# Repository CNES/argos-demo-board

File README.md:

# Argos Demo Board Using Arribada SMD Module

Demonstration and evaluation board designed to operate the **Arribada Argos SMD module** via USB and transmit **ARGOS uplink messages to the Kineis satellite constellation**.

---

> *© 2025/2026 CNES – Paul Miailhe.*  
> *This material is licensed under the CERN Open Hardware Licence Version 2 (CERN-OHL-S).*  
> *See licence: https://ohwr.org/licences/* 

> 
> 
> 
> 
> 
> 
---

---

## Introduction

This project presents an **Argos Transceiver Demonstration Board** intended for the evaluation, validation, and operation of the **Arribada Argos SMD module**.  
The board provides a compact and robust hardware platform to transmit **ARGOS uplink messages to the Kineis satellite constellation** using a standard **USB interface**.

Communication between the host computer and the Arribada SMD module is handled by a **FTDI FT231XQ USB-to-UART bridge**, directly interfacing with the module UART. This approach enables simple control of the transceiver using standard serial terminals or custom software tools.

The demonstration board integrates all essential functions required to operate the Arribada SMD module in a laboratory or development environment, including power supply conditioning, USB-to-UART communication, and RF interfacing. It is primarily intended to support early hardware validation, firmware development, and system-level testing of Argos communication chains prior to integration into a final embedded or avionics system.

This board targets engineers, students, and developers involved in **satellite communications, avionics, IoT, or space-related applications**, and may be used both as a standalone evaluation platform and as a reference hardware design.

---

> Inline with Arribada's open source philosophy, this board deliberately adopts a design distinct from the official demonstration hardware, focusing on simplicity and direct plug-and-play operation from a standard PC. The schematic and architecture are provided for reference, allowing potential users to reuse, adapt, or extend them according to their own needs..

---

## Hardware Design

### 1. Communication Architecture

Communication between the host PC and the **Arribada Argos SMD module** is performed through the module’s **UART interface**.  
This interface is used to send **AT commands** from a PC in order to configure the module and transmit **ARGOS uplink messages**. 
[→ See details on GitHub Arribada](https://github.com/arribada/argos-smd-at-kineis-firmware)

The USB-to-UART conversion is handled by a **FTDI FT231XQ USB 2.0 to UART bridge**. This device converts USB data received from a **virtual COM port** into UART signals fully compatible with the Arribada SMD module.

This architecture allows the board to be operated using:
- Standard serial terminal software
- Custom scripts
- Dedicated test or validation tools

No additional embedded controller is required, which simplifies early testing and debugging.

---

### 2. Power Supply Architecture

The card supports two power supply modes to suit different uses.

#### 2.1 Power Source Selection

Power source selection is performed using the **JP1 jumper**, which allows switching between:
- **VBUS → VDD (5V)** supplied by the **USB-C port**
- **VOUT → VDD (5V)** supplied via the **external power input on connector J1**

#### 2.2 External Power Protection

The external power input on **connector J1** is protected by:
- A **resettable PTC fuse 1206L050YR**
- A **LTC4365 protection circuit**

The **LTC4365** provides:
- **Reverse polarity protection**
- **Undervoltage protection** with a threshold set to **2.5 V**
- **Overvoltage protection** for input voltages exceeding **5 V**

#### 2.3 Power Regulation

After the protection stage, the power rail is distributed to two **TPS63900 buck-boost converters**:
- One converter supplies the **RF power amplifier (PA)** and is **enabled and controlled directly by the Arribada SMD module**
- The second converter is **always enabled** and provides the regulated **3.3 V supply** required for the **Arribada SMD module logic**

---

### 3. Connector Types

The Argos Demo Board uses the following connector families:

- **USB4085-GF-A (GCT)**  
  **USB Type-C receptacle (16-pin)** used for:
  - USB 2.0 communication with the host PC
  - Board power supply via **VBUS**

- **JST B2B-XH series**  
  **Through-hole wire-to-board connectors** used for:
  - External power input (**2.5 V to 5 V**)
  - Digital interfaces (**UART, SPI, GPIO – 3.3 V logic**)
  - General-purpose I/O connections

- **FTSH-105-01-L-DV-K (Samtec)**  
  **10-pin JTAG connector** used for:
  - Programming
  - Low-level debugging of the **Arribada Argos SMD module**
  - Access to **JTAG/SWD signals** of the embedded **STM32WL55**

- **60312002114503 (Würth Elektronik)**  
  **SMA 50 Ω RF connector** used for:
  - RF output connection
  - External antenna interface for the **ARGOS frequency band**
  - ⚠️ When transmitting, it is important to have at least a 50 Ohm load connected to the antenna output to protect against impedance mismatch. 

---

### 4. Functional Diagram

---
## Summary of the Bill of Materials (BOM) 

Components used on the board, with their official datasheets:

| Reference | Part Number | Role / Function | Datasheet |
|-----------|-------------|-----------------|-----------|
| D1, D7 | SMAJ15CA | TVS diode for surge and ESD protection | [→ Datasheet Littelfuse](https://www.littelfuse.com/assetdocs/tvs-diodes-smaj-datasheet?assetguid=13c2a823-03b8-4d1f-9ddc-9b44670aed9d) |
| F1, F2 | 1206L035/16YR | Resettable PTC fuse (overcurrent protection) | [→ Datasheet Littelfuse](https://www.littelfuse.com/assetdocs/resettable-ptcs-1206l-datasheet?assetguid=39a3f0c5-1a6b-4d52-9b9b-5c9c5f9c9c4a) |
| FB1, FB2 | BLM18KG601SN1D | Ferrite bead for EMI suppression | [→ Datasheet Murata](https://pim.murata.com/en-eu/pim/details/?partNum=BLM18KG601SN1%23) |
| L4 | 744232090 | Common-mode choke for USB line filtering | [→ Datasheet Würth Elektronik](https://www.we-online.com/components/products/datasheet/744232090.pdf) |
| Q1, Q2 | BSN20 | N-channel MOSFET for switching and protection | [→ Datasheet DIODES INC.](http://www.diodes.com/assets/Datasheets/ds31898.pdf) |
| SW1 | PTS647 | Momentary tactile push button switch | [→ Datasheet C&K](https://www.ckswitches.com/media/1471/pts647.pdf) |
| U2 | LTC4365DDB | Overvoltage, undervoltage and reverse polarity protection IC | [→ Datasheet Analog Devices](https://www.analog.com/media/en/technical-documentation/data-sheets/4365fa.pdf) |
| U3, U4 | TPS63900 | Buck-boost DC/DC converters | [→ Datasheet Texas Instruments](https://www.ti.com/lit/ds/symlink/tps63900.pdf) |
| U5 | 82400102 | Low-capacitance TVS diode array for USB protection | [→ Datasheet Würth Elektronik](https://www.we-online.com/components/products/datasheet/82400102.pdf) |
| U6 | FT231XQ | USB-to-UART bridge | [→ Datasheet FTDI](https://www.ftdichip.com/Support/Documents/DataSheets/ICs/DS_FT231X.pdf) |
| H4 | 3610213126S | RF shielding cabinet | [→ Datasheet Würth Elektronik](https://www.we-online.com/catalog/datasheet/3610213126S.pdf) |
| J8 | USB4085-GF-A | USB 2.0-only 16P Type-C Receptacle connector | [→ Datasheet GCT](https://www.usb.org/sites/default/files/documents/usb_type-c.zip) |
| J2 | 60312002114503 | Coaxial connector SMA | [→ Datasheet Würth Elektronik](https://www.we-online.com/components/products/datasheet/60312002114503.pdf?srsltid=AfmBOorv9MzbrmPnU-04R523FjHEC69xDMjVUBnj-GW9FHYse90msupc) |
| J4 | FTSH-105-01-L-DV-K | JTAG 10-PINS | [→ Datasheet Samtec](https://suddendocs.samtec.com/catalog_english/ftsh_smt.pdf?_gl=1*muazsd*_gcl_au*MTcxOTU2ODE1My4xNzY3ODg0MzAy*_ga*MTU3MjM5MTY3NS4xNzY3ODg0MzAz*_ga_3KFNZC07WW*czE3Njc4ODQzMDIkbzEkZzAkdDE3Njc4ODQzMDIkajYwJGwwJGgxMjE2ODMwMTY0) |
| J1, J3, J5, J6, J7 | B2B-XH | Through-hole wire-to-board connectors | [→ Datasheet JST](https://www.jst.fr/core/file.get?path=doc/jst/family/pdf/exh0125.pdf) |
| U1 | Argos SMD module | Transceiver Argos SMD for uplink Argos satellite | [→ Datasheet Arribada](https://github.com/arribada/featherwings-argos-smd-hw/wiki) |

---

## Getting Started

1. Connect the demonstration board to a host computer using a USB cable.
2. Install the **FTDI drivers** if required.
3. Select the desired **power input** using the **JP1 jumper**.
4. Connect an **antenna or a 50 Ω RF load** to the **SMA connector** before powering the board.
5. Open a **serial terminal** or a **custom software tool** on the host computer.
6. Configure the serial port according to the **Arribada Argos SMD module specifications**.
7. Send **AT commands** to configure the module and transmit **ARGOS uplink messages**.
8. If the board is operating correctly, the **5 V and 3.3 V LEDs** should be ON, and **TX/RX activity LEDs** should indicate serial communication.

Refer to the Arribada SMD module documentation for command syntax and operational details.

---

## Regulatory and Operational Notice

ARGOS transmissions are subject to regulatory constraints and operational authorization.

- Transmission over the ARGOS / Kineis constellation may require prior approval
- Users are responsible for ensuring compliance with applicable regulations
- This board does not grant any transmission rights by itself

---

## Mechanical Characteristics

- Dimensions: **80 × 50 mm**
- Maximum thickness: **13.5 mm**
- Mounting holes: 4 × Ø3.2 mm
- Weight without bracket: ** g**
- **STEP 3D** file available here:

---

## Regulatory and Operational Notice

ARGOS transmissions are subject to regulatory and operational constraints.

- Transmission over the ARGOS / Kineis constellation require prior authorization
- Users are responsible for regulatory compliance
- This board does **not** grant transmission rights by itself

---

## References & Resources

- **Arribada Initiative** – Official site  
  See link: <https://arribada.org>

- **Official Argos SMD Arduino Demo** – by Arribada  
  The full Arduino-based demonstration for the Argos SMD module is available on GitHub.  
  See link: <https://github.com/arribada/argos-smd-test-arduino>

- **Official Breakout Board FeatherWings** – by Arribada  
  This breakout board can be used with a Feather board (from Adafruit) to connect the ARGOS-SMD module.  
  It exposes the ARGOS-SMD module pins to the Feather board and includes a dedicated LDO to power the RF amplifier.  
  See link: <https://github.com/arribada/featherwings-argos-smd-hw>

- **Official Argos SMD Hardware Module** – by Arribada  
  The Arribada Argos SMD module is a compact **20 × 20 mm PCB** designed to operate as a standalone module or co-processor, enabling satellite communication via the **Kineis network**.  
  See link: <https://github.com/arribada/argos-smd-hw>

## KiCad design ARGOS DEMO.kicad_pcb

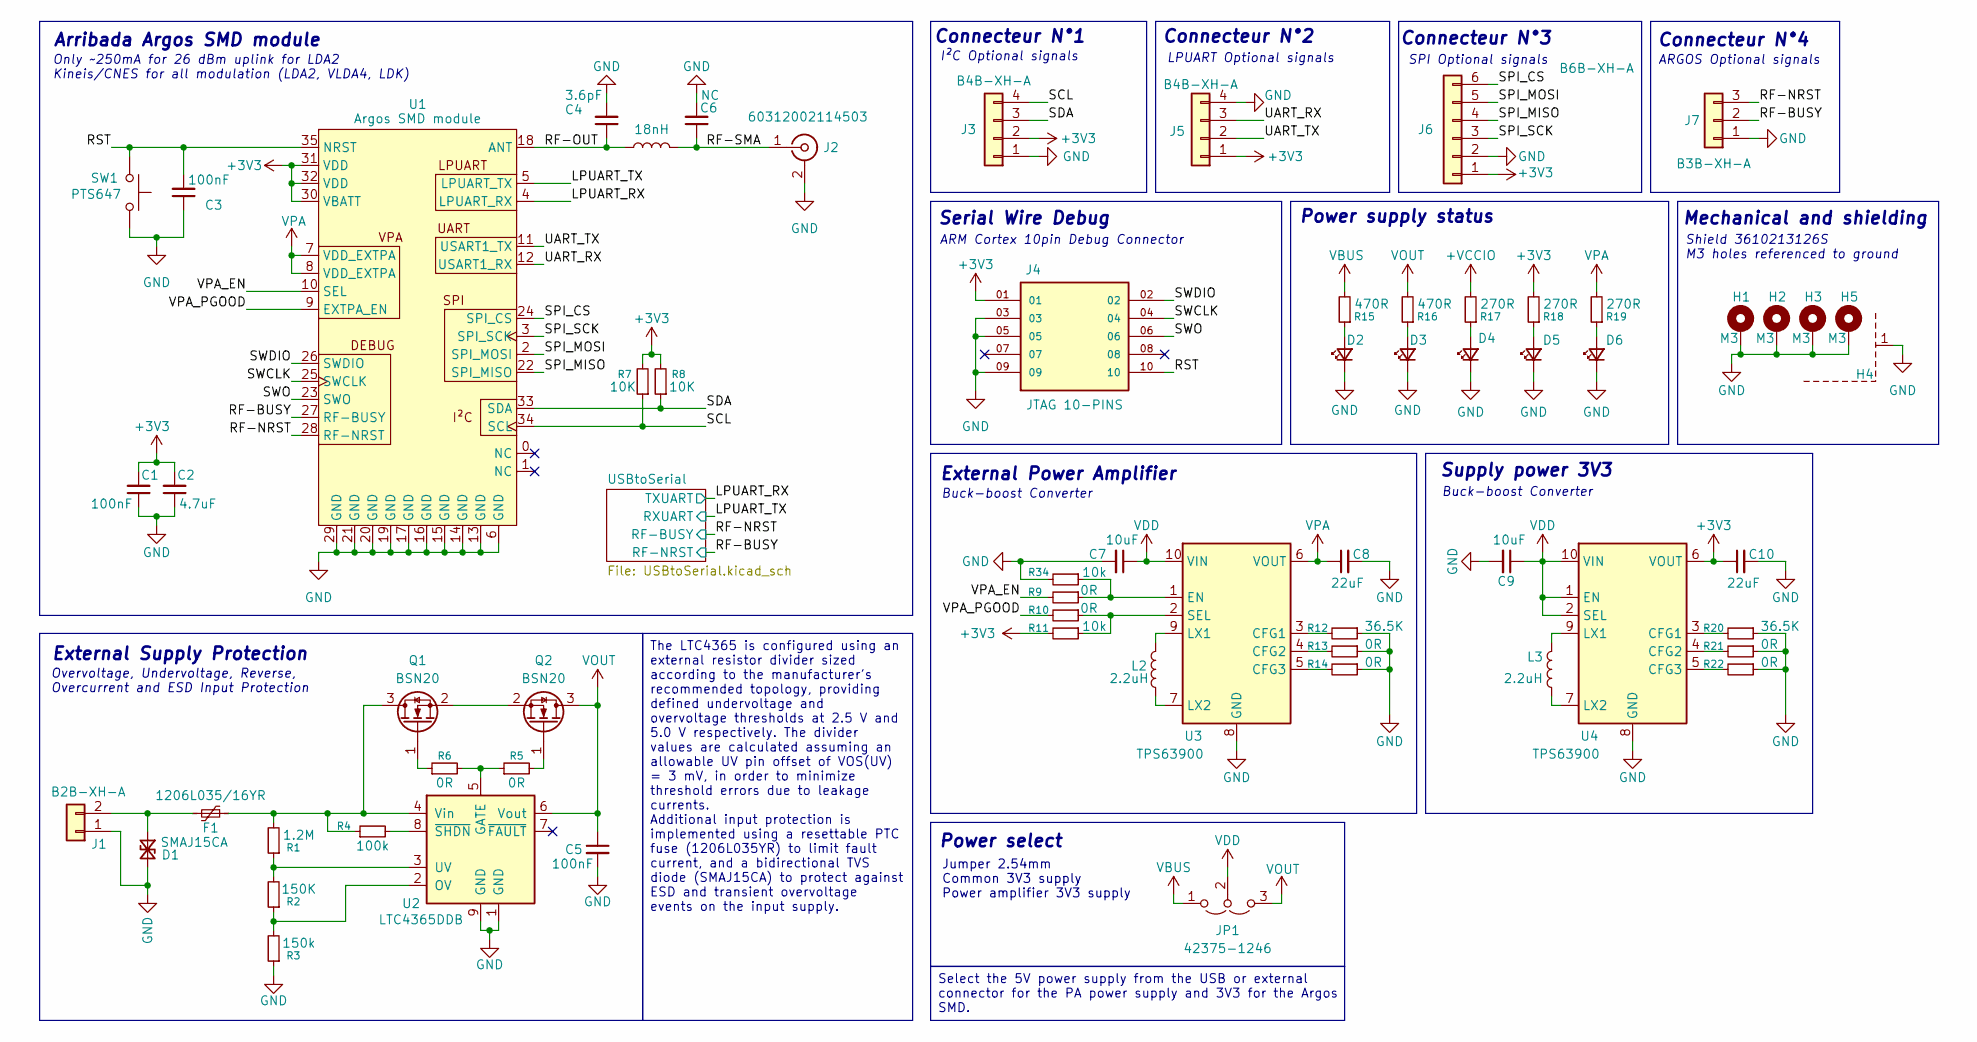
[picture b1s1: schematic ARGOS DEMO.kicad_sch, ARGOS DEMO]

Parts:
C1, C3, C5: 100nF; C_0603_1608Metric
C2: 4.7uF; C_0603_1608Metric
C4: 3.6pF; C_0603_1608Metric
C6: NC; C_0603_1608Metric
C7, C9: 10uF; C_0603_1608Metric
C8, C10: 22uF; C_0805_2012Metric
D1: SMAJ15CA; D_SMA
D2, D3, D4, D5, D6: LED_Small; LED_0603_1608Metric
F1: 1206L035/16YR; Fuse_1206_3216Metric
H1, H2, H3, H5: M3; MountingHole_3.2mm_M3_DIN965_Pad
H4: 3610213126S; H_Wurth_WE-SHC-SMT-FRAME_36103255S; Part Number 3610213126S
J1: B2B-XH-A; JST_XH_B2B-XH-A_1x02_P2.50mm_Vertical
J2: 60312002114503; SMA_Wurth_60312002114503_Vertical
J3, J5: B4B-XH-A; JST_XH_B4B-XH-A_1x04_P2.50mm_Vertical
J4: JTAG 10-PINS; SAMTEC_FTSH-105-XX-X-DV
J6: B6B-XH-A; JST_XH_B6B-XH-A_1x06_P2.50mm_Vertical
J7: B3B-XH-A; JST_XH_B3B-XH-A_1x03_P2.50mm_Vertical
JP1: 42375-1246; PinHeader_1x03_P2.54mm_Vertical
L1: 18nH; L_0603_1608Metric
L2, L3: 2.2uH; L_1008_2520Metric
Q1, Q2: BSN20; SOT-23
R1: 1.2M; R_0603_1608Metric
R2: 150K; R_0603_1608Metric
R3: 150k; R_0603_1608Metric
R4: 100k; R_0603_1608Metric
R5, R6, R9, R10, R13, R14, R21, R22: 0R; R_0603_1608Metric
R7, R8: 10K; R_0603_1608Metric
R11, R34: 10k; R_0603_1608Metric
R12, R20: 36.5K; R_0603_1608Metric
R15, R16: 470R; R_0603_1608Metric
R17, R18, R19: 270R; R_0603_1608Metric
SW1: PTS647; SW_SPST_PTS647_Sx38
U1: Argos SMD module; SMD ARGOS
U2: LTC4365DDB; DFN-8-1EP_2x3mm_P0.5mm_EP0.61x2.2mm
U3, U4: TPS63900; WSON-10-1EP_2.5x2.5mm_P0.5mm_EP1.2x2mm

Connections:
+3V3: C1.2, C2.2, C10.1, J3.2, J4.01, J5.1, J6.1, R7.2, R8.2, R11.2, R18.2, U1.30 (VBATT), U1.31 (VDD), U1.32 (VDD), U4.6 (VOUT)
+VCCIO: R17.2; also elsewhere on the board
/LPUART_RX: U1.4 (LPUART_RX); also elsewhere on the board
/LPUART_TX: U1.5 (LPUART_TX); also elsewhere on the board
/RF-BUSY: J7.2, U1.27 (RF-BUSY); also elsewhere on the board
/RF-NRST: J7.3, U1.28 (RF-NRST); also elsewhere on the board
/RF-OUT: C4.1, L1.1, U1.18 (ANT)
/RF-SMA: C6.1, J2.1 (In), L1.2
/RST: C3.2, J4.10, SW1.1, U1.35 (NRST)
/SCL: J3.4, R7.1, U1.34 (SCL)
/SDA: J3.3, R8.1, U1.33 (SDA)
/SPI_CS: J6.6, U1.24 (SPI_CS)
/SPI_MISO: J6.4, U1.22 (SPI_MISO)
/SPI_MOSI: J6.5, U1.2 (SPI_MOSI)
/SPI_SCK: J6.3, U1.3 (SPI_SCK)
/SWCLK: J4.04, U1.25 (SWCLK)
/SWDIO: J4.02, U1.26 (SWDIO)
/SWO: J4.06, U1.23 (SWO)
/UART_RX: J5.3, U1.12 (USART1_RX)
/UART_TX: J5.2, U1.11 (USART1_TX)
/VPA_EN: R9.2, U1.10 (SEL)
/VPA_PGOOD: R10.2, U1.9 (EXTPA_EN)
GND: C1.1, C2.1, C3.1, C4.2, C5.2, C6.2, C7.2, C8.2, C9.2, C10.2, D1.2 (A2), D2.1 (K), D3.1 (K), D4.1 (K), D5.1 (K), D6.1 (K), H1.1, H2.1, H3.1, H4.1 (GND), H5.1, J1.1, J2.2 (Ext), J3.1, J4.03, J4.05, J4.09, J5.4, J6.2, J7.1, R3.1, R12.1, R13.1, R14.1, R20.1, R21.1, R22.1, R34.2, SW1.2, U1.6 (GND), U1.13 (GND), U1.14 (GND), U1.15 (GND), U1.16 (GND), U1.17 (GND), U1.19 (GND), U1.20 (GND), U1.21 (GND), U1.29 (GND), U2.1 (GND), U2.9 (GND), U3.8 (GND), U3.11 (GND), U4.8 (GND), U4.11 (GND); also elsewhere on the board
unnamed: D1.1 (A1), F1.2, J1.2
unnamed: D2.2 (A), R15.1
unnamed: D3.2 (A), R16.1
unnamed: D4.2 (A), R17.1
unnamed: D5.2 (A), R18.1
unnamed: D6.2 (A), R19.1
unnamed: F1.1, Q1.3 (D), R1.2, R4.1, U2.4 (Vin)
unnamed: Q1.1 (G), R6.1
unnamed: Q1.2 (S), Q2.2 (S)
unnamed: Q2.1 (G), R5.2
unnamed: R5.1, R6.2, U2.5 (GATE)
unnamed: R2.1, R3.2, U2.2 (OV)
unnamed: R1.1, R2.2, U2.3 (UV)
unnamed: R4.2, U2.8 (~SHDN)
unnamed: R12.2, U3.3 (CFG1)
unnamed: R13.2, U3.4 (CFG2)
unnamed: R14.2, U3.5 (CFG3)
unnamed: R9.1, R34.1, U3.1 (EN)
unnamed: L2.2, U3.9 (LX1)
unnamed: L2.1, U3.7 (LX2)
unnamed: R10.1, R11.1, U3.2 (SEL)
unnamed: R20.2, U4.3 (CFG1)
unnamed: R21.2, U4.4 (CFG2)
unnamed: R22.2, U4.5 (CFG3)
unnamed: L3.2, U4.9 (LX1)
unnamed: L3.1, U4.7 (LX2)
VBUS: JP1.1 (A), R15.2; also elsewhere on the board
VDD: C7.1, C9.1, JP1.2 (C), U3.10 (VIN), U4.1 (EN), U4.2 (SEL), U4.10 (VIN)
VOUT: C5.1, JP1.3 (B), Q2.3 (D), R16.2, U2.6 (Vout)
VPA: C8.1, R19.2, U1.7 (VDD_EXTPA), U1.8 (VDD_EXTPA), U3.6 (VOUT)

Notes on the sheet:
SPI Optional signals
Shield 3610213126S M3 holes referenced to ground
ARGOS Optional signals
Connecteur N°3
Mechanical and shielding
External Power Amplifier
Serial Wire Debug
Overvoltage, Undervoltage, Reverse, Overcurrent and ESD Input Protection
Connecteur N°1
Connecteur N°2
I²C Optional signals
Supply power 3V3
Buck-boost Converter
Jumper 2.54mm Common 3V3 supply Power amplifier 3V3 supply
Power select
Only ~250mA for 26 dBm uplink for LDA2 Kineis/CNES for all modulation (LDA2, VLDA4, LDK)
Power supply status
Connecteur N°4
Arribada Argos SMD module
LPUART Optional signals
External Supply Protection
ARM Cortex 10pin Debug Connector
Select the 5V power supply from the USB or external connector for the PA power supply and 3V3 for the Argos SMD.
The LTC4365 is configured using an external resistor divider sized according to the manufacturer's recommended topology, providing defined undervoltage and overvoltage thresholds at 2.5 V and 5.0 V respectively. The divider values are calculated assuming an allowable UV pin offset of VOS(UV) = 3 mV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

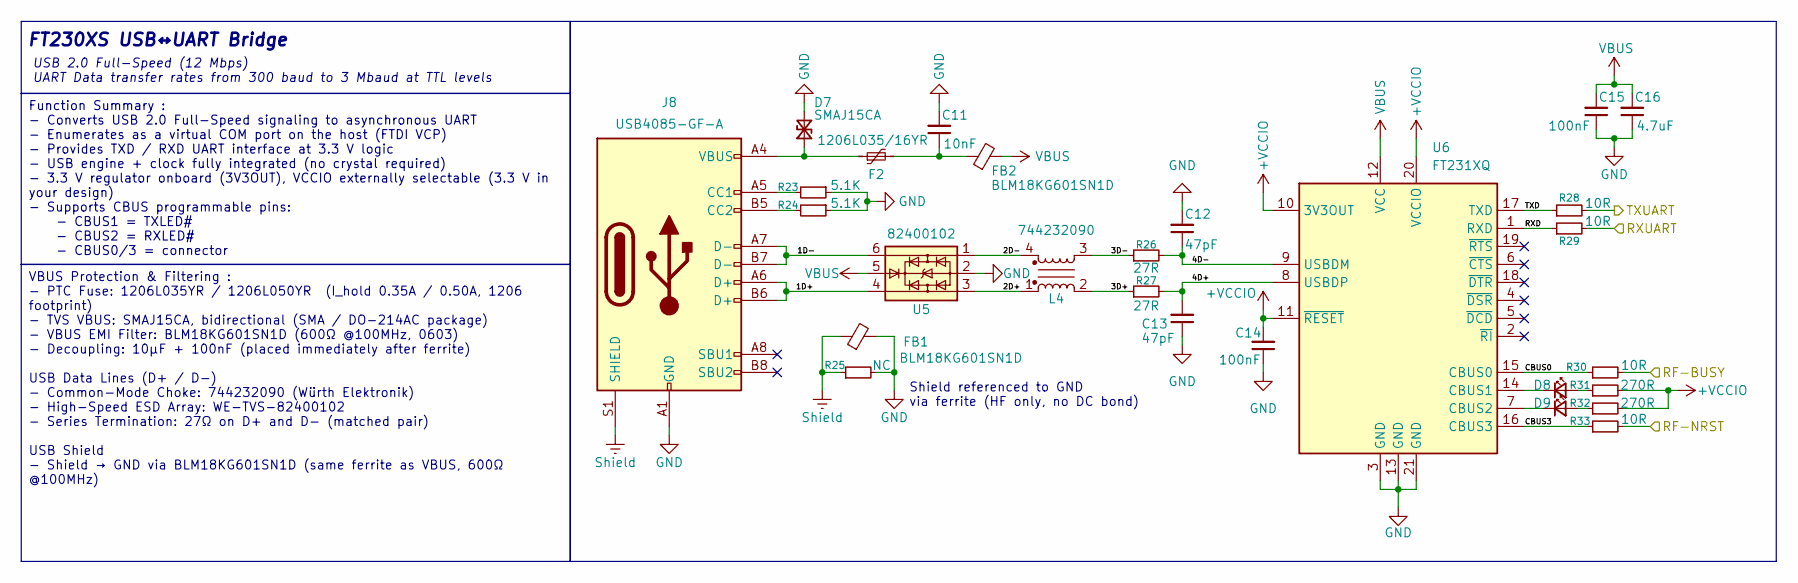
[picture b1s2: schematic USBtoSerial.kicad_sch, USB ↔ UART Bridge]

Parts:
C11: 10nF; C_0603_1608Metric
C12, C13: 47pF; C_0603_1608Metric
C14, C15: 100nF; C_0603_1608Metric
C16: 4.7uF; C_0603_1608Metric
D7: SMAJ15CA; D_SMA
D8, D9: LED_Small; LED_0603_1608Metric
F2: 1206L035/16YR; Fuse_1206_3216Metric
FB1, FB2: BLM18KG601SN1D; L_0603_1608Metric
J8: USB4085-GF-A; CONN16_USB4085-GF-A_GCT
L4: 744232090; L_CommonMode_Wurth_WE-CNSW-1206
R23, R24: 5.1K; R_0603_1608Metric
R25: NC; R_0603_1608Metric
R26, R27: 27R; R_0603_1608Metric
R28, R29, R30, R33: 10R; R_0603_1608Metric
R31, R32: 270R; R_0603_1608Metric
U5: 82400102; SOT-23-6
U6: FT231XQ; QFN-20-1EP_4x4mm_P0.5mm_EP2.5x2.5mm

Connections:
+VCCIO: C14.2, R31.2, R32.2, U6.10 (3V3OUT), U6.11 (~RESET), U6.20 (VCCIO); also elsewhere on the board
/LPUART_RX: R28.2; also elsewhere on the board
/LPUART_TX: R29.2; also elsewhere on the board
/RF-BUSY: R33.2; also elsewhere on the board
/RF-NRST: R30.2; also elsewhere on the board
/USBtoSerial/1D+: J8.A6 (D+), J8.B6 (D+), U5.4
/USBtoSerial/1D-: J8.A7 (D-), J8.B7 (D-), U5.6
/USBtoSerial/2D+: L4.1, U5.3
/USBtoSerial/2D-: L4.4, U5.1
/USBtoSerial/3D+: L4.2, R27.1
/USBtoSerial/3D-: L4.3, R26.1
/USBtoSerial/4D+: C13.2, R27.2, U6.8 (USBDP)
/USBtoSerial/4D-: C12.1, R26.2, U6.9 (USBDM)
/USBtoSerial/CBUS0: R30.1, U6.15 (CBUS0)
/USBtoSerial/CBUS3: R33.1, U6.16 (CBUS3)
/USBtoSerial/RXD: R29.1, U6.1 (RXD)
/USBtoSerial/TXD: R28.1, U6.17 (TXD)
GND: C11.2, C12.2, C13.1, C14.1, C15.1, C16.1, D7.2 (A2), FB1.2, J8.A1 (GND), J8.A12 (GND), J8.B1 (GND), J8.B12 (GND), R23.1, R24.1, R25.2, U5.2, U6.3 (GND), U6.13 (GND), U6.21 (GND); also elsewhere on the board
unnamed: C11.1, F2.2, FB2.1
unnamed: D7.1 (A1), F2.1, J8.A4 (VBUS), J8.A9 (VBUS), J8.B4 (VBUS), J8.B9 (VBUS)
unnamed: D8.2 (A), R31.1
unnamed: D8.1 (K), U6.14 (CBUS1)
unnamed: D9.2 (A), R32.1
unnamed: D9.1 (K), U6.7 (CBUS2)
unnamed: J8.A5 (CC1), R23.2
unnamed: J8.B5 (CC2), R24.2
Shield: FB1.1, J8.S1 (SHIELD), R25.1
VBUS: C15.2, C16.2, FB2.2, U5.5, U6.12 (VCC); also elsewhere on the board

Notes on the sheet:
USB 2.0 Full-Speed (12 Mbps) UART Data transfer rates from 300 baud to 3 Mbaud at TTL levels
Shield referenced to GND via ferrite (HF only, no DC bond)
FT230XS USB↔UART Bridge
Function Summary : - Converts USB 2.0 Full-Speed signaling to asynchronous UART - Enumerates as a virtual COM port on the host (FTDI VCP) - Provides TXD / RXD UART interface at 3.3 V logic - USB engine + clock fully integrated (no crystal required) - 3.3 V regulator onboard (3V3OUT), VCCIO external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
VBUS Protection & Filtering : - PTC Fuse: 1206L035YR / 1206L050YR (I_hold 0.35A / 0.50A, 1206 footprint) - TVS VBUS: SMAJ15CA, bidirectional (SMA / DO-214AC package) - VBUS EMI Filter: BLM18KG601SN1D (600Ω @100MHz, 0603) - Decoupling: 10µF + 100nF (placed immediately after ferrite) USB Data Lines (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

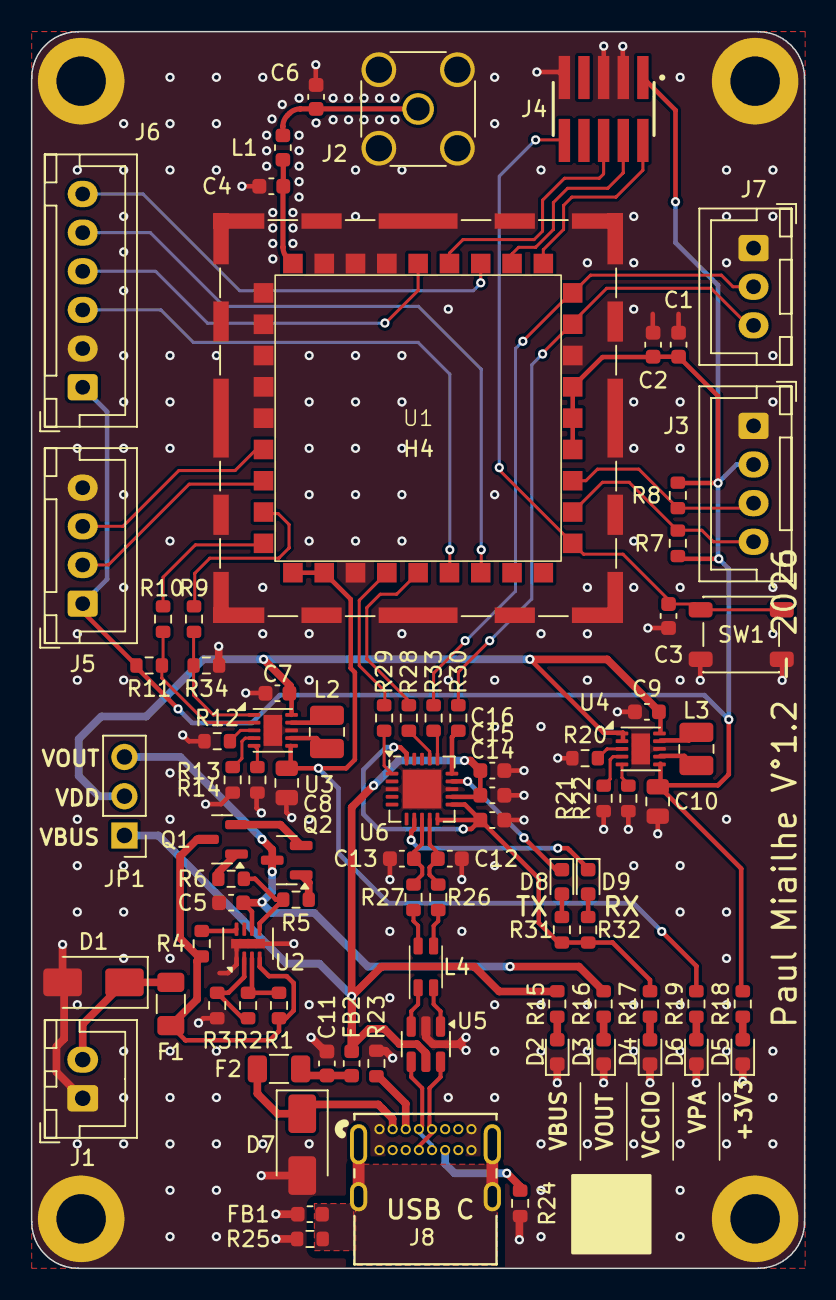
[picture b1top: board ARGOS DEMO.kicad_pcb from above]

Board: 4 copper layers, 50.0 x 80.0 mm, 90 parts (0 on the bottom side), 74 nets.

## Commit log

2026-01-29 Add LICENSE
2026-02-24 Correction USART vers le LPUART
2026-02-24 Correction doc
2026-02-24 Correction doc 2
2026-02-24 update doc
2026-04-11 Create .ohwr.yaml for submit project to OHWR
    Added project metadata and links in .ohwr.yaml.
2026-04-27 Create iBom.html
    Add HTLM Page of Bill of Materials (BOM) listing with the ability to visually correlate and easily search for components and their placements
2026-04-27 Rename ibom.html to index.html
2026-04-27 feat: Add Argos I-Bom
2026-04-27 style: Renamed Public to /docs
2026-04-27 feat: Added readme as page
2026-04-27 Change Jekyll source directory to './docs'
2026-04-27 chore: Moved images to /docs
2026-04-27 feat: Added some style to the main page
2026-04-27 feat: Added one section for schematics
2026-04-27 chore: Change folder name
2026-04-27 fix: Image link in readme
2026-04-27 Change project image URL in .ohwr.yaml
    Updated image URL to point to the new location.
2026-04-27 chore: change website visuel
2026-04-27 feat: change description
2026-04-27 feat: change description text
2026-04-27 fix: bug readme html
2026-04-27 Fix license link formatting in README.md
2026-04-27 Update README with badges and additional information
    Added badges for licensing, website, and partners.
2026-04-27 Enhance BOM section with interactive badge
    Added an interactive BOM badge and updated the BOM section.

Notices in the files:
README.md:
License: CERN-OHL-S
